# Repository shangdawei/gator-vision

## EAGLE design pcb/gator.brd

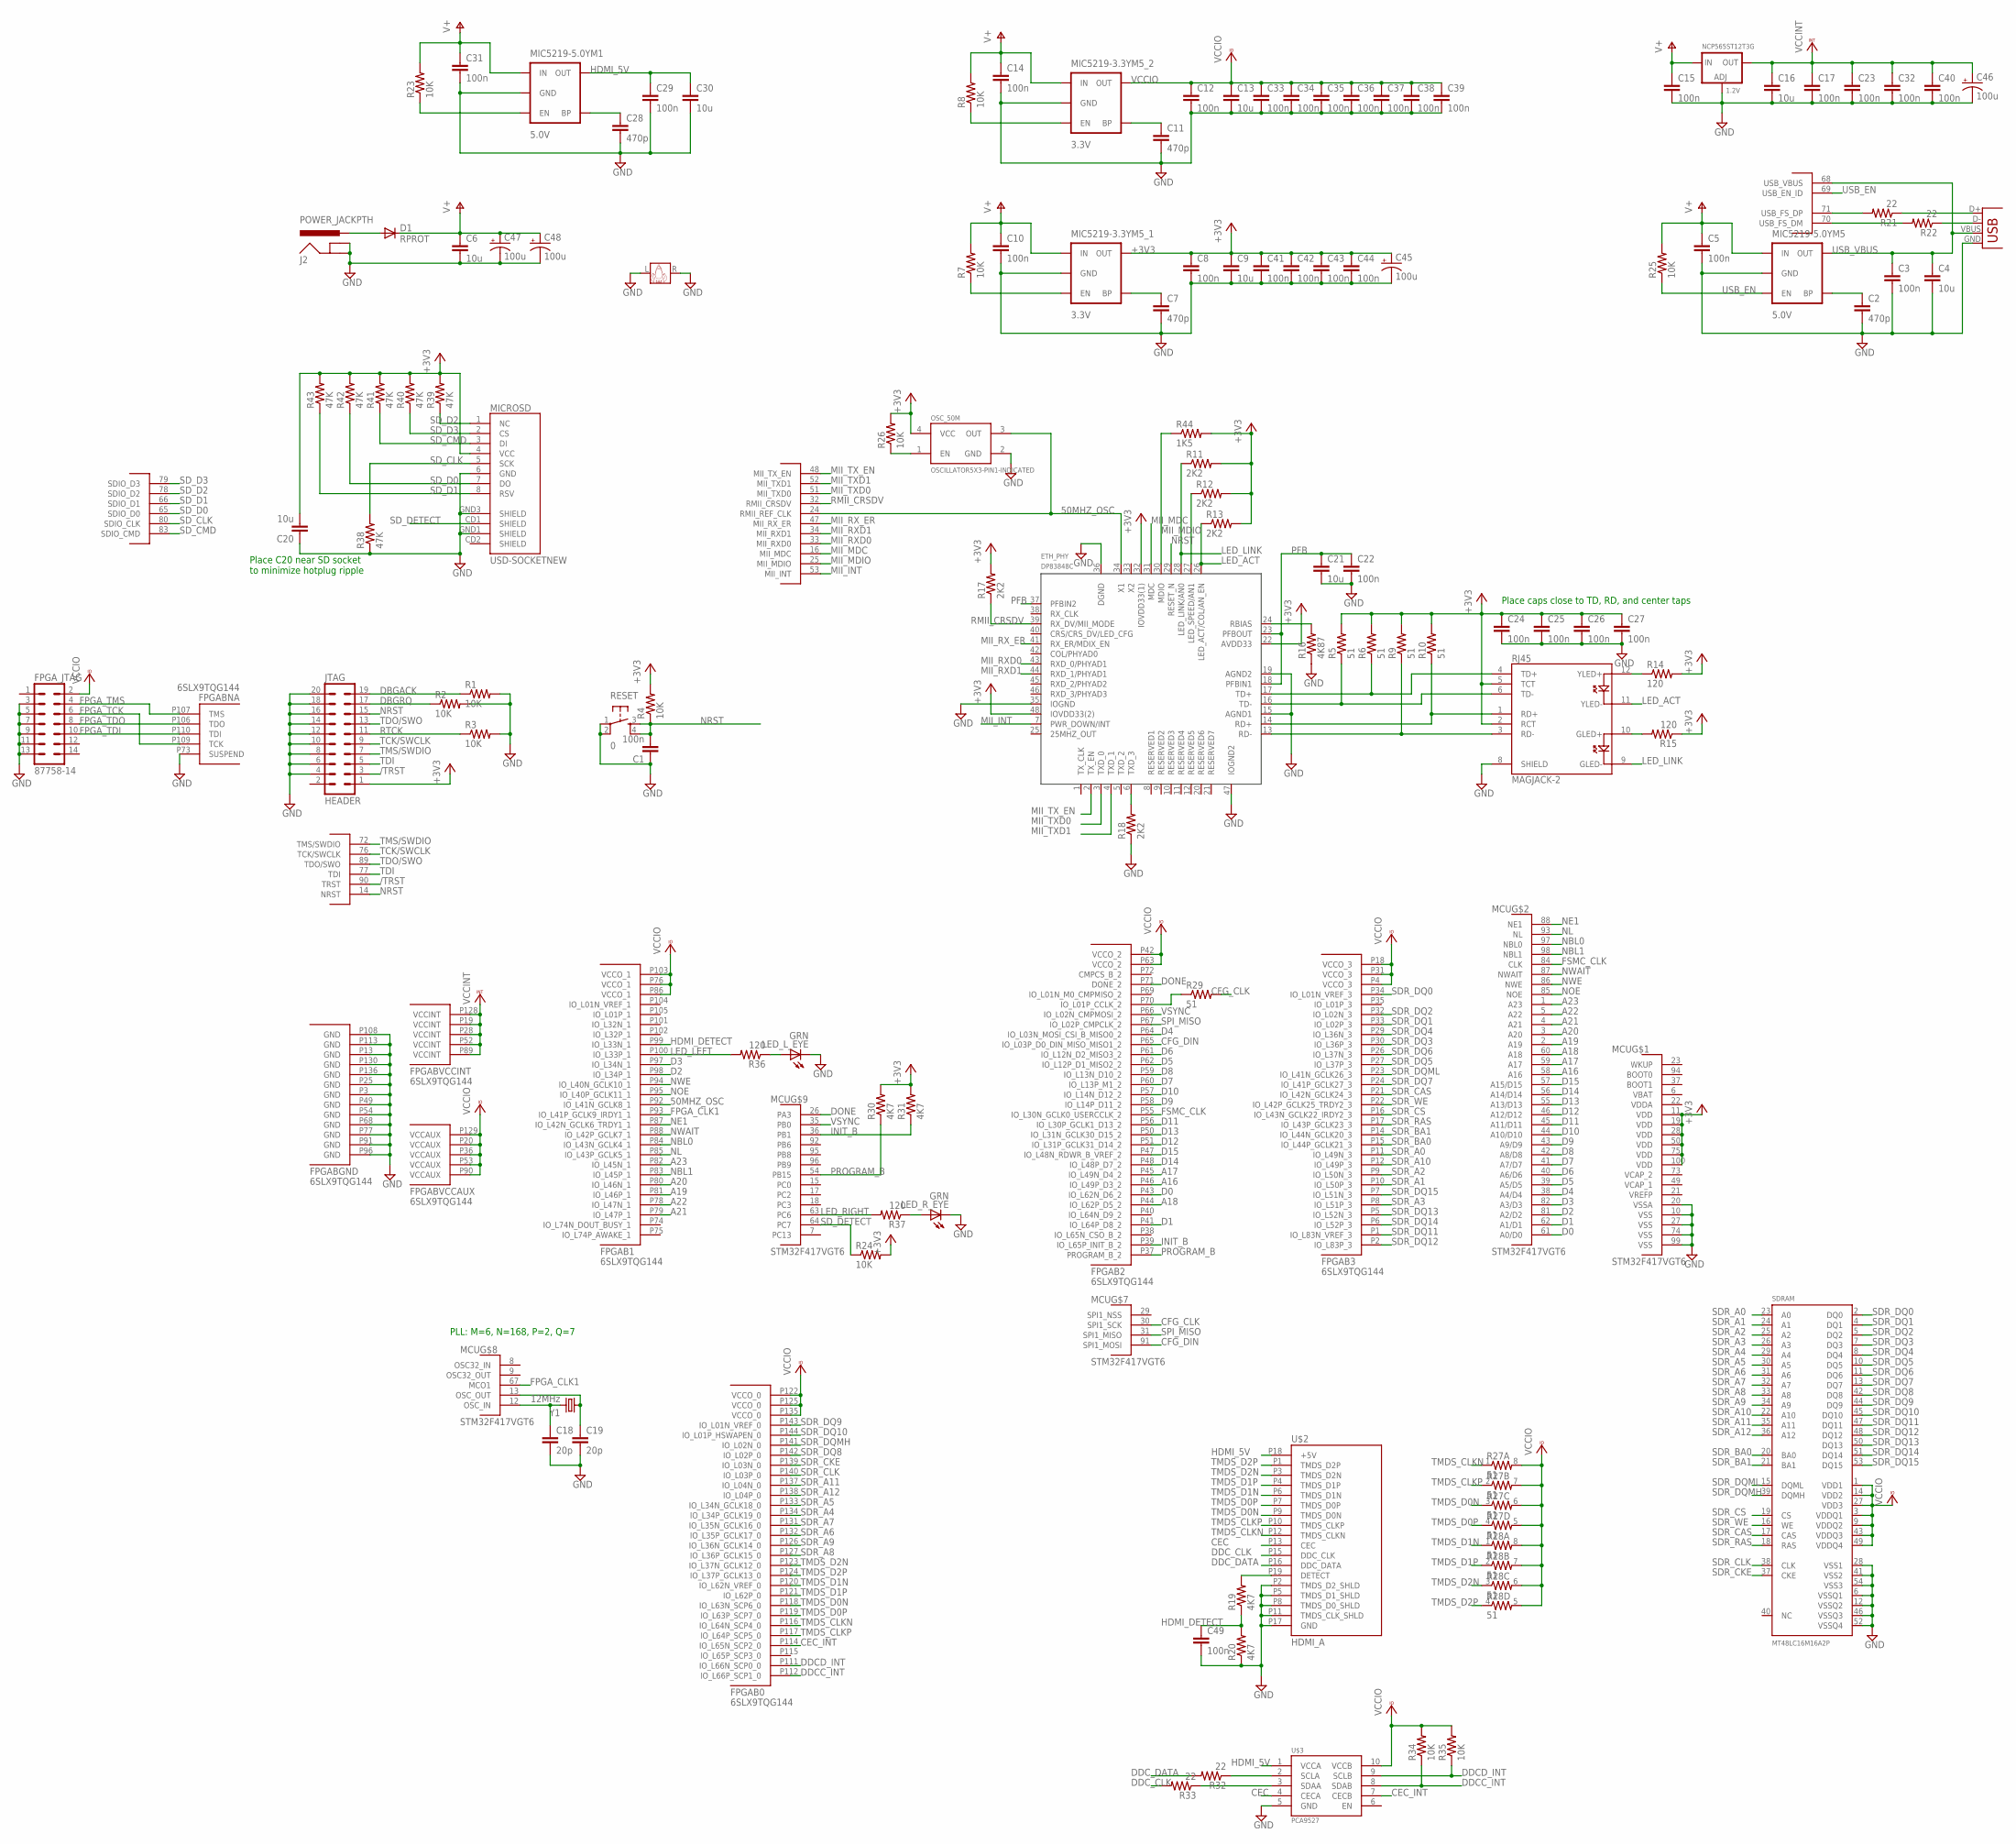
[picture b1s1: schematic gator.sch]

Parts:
C1, C3, C5, C8, C10, C12, C14, C15, C17, C22, C23, C24, C25, C26, C27, C29, C31, C32, C33, C34, C35, C36, C37, C38, C39, C40, C41, C42, C43, C44, C49: 100n; 0603-CAP
C2, C7, C11, C28: 470p; 0603-CAP
C4, C6, C9, C13, C16, C20, C21, C30: 10u; 0603-CAP
C18, C19: 20p; 0603-CAP
C45, C46, C47, C48: 100u; CPOL-RADIAL-100UF-25V
D1: RPROT; DIODE-1N4001; DIGIKEY# 497-6588-1-ND
ETH_PHY: DP83848C; LQFP-48; MOUSER# 926-DP83848CVVX/NOPB; DIGIKEY# DP83848CVVX/NOPBCT-ND
FPGA: 6SLX9TQG144; TQ144; DIGIKEY# 122-1745-ND
FPGA_JTAG: 87758-14; DIGIKEY# AE10561-ND
J2: POWER_JACKPTH; POWER_JACK_PTH; DIGIKEY# CP-002A-ND
JTAG: HEADER; ML20; DIGIKEY# S9172-ND
LED_L_EYE: GRN; LED3MM; DIGIKEY# 160-1659-ND
LED_R_EYE: GRN; LED3MM; DIGIKEY# 160-1659-ND
MCU: STM32F417VGT6; LQFP-100; DIGIKEY# 497-11900-ND
MIC5219-3.3YM5_1, MIC5219-3.3YM5_2: 3.3V; SOT23-5; DIGIKEY# 576-1281-1-ND
MIC5219-5.0YM1, MIC5219-5.0YM5: 5.0V; SOT23-5; DIGIKEY# 576-2770-1-ND
MICROSD: USD-SOCKETNEW; MICRO-SD-SOCKET-PP; DIGIKEY# 101-00660-68-6-1-ND
NCP565ST12T3G: 1.2V; SOT223-R; DIGIKEY# NCP565ST12T3GOSCT-ND
OSC_50M: OSCILLATOR5X3-PIN1-INDICATED; CRYSTAL-OSC-SMD-5X3; DIGIKEY# CTX1011CT-ND
R1, R2, R3, R4, R7, R8, R23, R24, R25, R26, R34, R35: 10K; 0603-RES
R5, R6, R9, R10, R29: 51; 0603-RES
R11, R12, R13, R17, R18: 2K2; 0603-RES
R14, R15, R36, R37: 120; 0603-RES
R16: 4K87; 0603-RES
R19, R20, R30, R31: 4K7; 0603-RES
R21, R22, R32, R33: 22; 0603-RES
R27, R28: 51; 0603-ARV; DIGIKEY# YC164J-51CT-ND
R38, R39, R40, R41, R42, R43: 47K; 0603-RES
R44: 1K5; 0603-RES
RESET: 0; TACTILE-PTH
RJ45: MAGJACK-2; MAGJACK-19938; DIGIKEY# 380-1103-ND
SDRAM: MT48LC16M16A2P; TSOP54-400; MOUSER# 913-AS4C16M16S-6TAN; DIGIKEY# 557-1223-1-ND
U$2: HDMI_A; HDMI_A_SMT; DIGIKEY# WM19084CT-ND
U$3: PCA9527; TSSOP10; DIGIKEY# 568-4770-1-ND
U$4: GATOR_HEAD; DIGIKEY# T1065-P5P-ND
X1: USB-A-S; DIGIKEY# 1175-1016-ND
Y1: 12MHz; HC49US; DIGIKEY# CTX904-ND

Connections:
50MHZ_OSC: ETH_PHY.34 (X1), FPGA.P92 (IO_L41N_GCLK8_1), MCU.24 (RMII_REF_CLK), OSC_50M.3 (OUT)
+3V3: C8.1, C9.1, C20.2, C24.1, C25.1, C26.1, C27.1, C41.1, C42.1, C43.1, C44.1, C45.1 (+), ETH_PHY.22 (AVDD33), ETH_PHY.32 (IOVDD33(1)), ETH_PHY.48 (IOVDD33(2)), JTAG.1, MCU.11 (VDD), MCU.19 (VDD), MCU.28 (VDD), MCU.50 (VDD), MCU.75 (VDD), MCU.100 (VDD), MIC5219-3.3YM5_1.5 (OUT), MICROSD.4 (VCC), OSC_50M.4 (VCC), R4.2, R5.2, R6.2, R9.2, R10.2, R11.2, R12.2, R13.2, R14.2, R15.1, R17.2, R24.2, R26.2, R30.2, R31.2, R39.2, R40.2, R41.2, R42.2, R43.2, R44.2, RJ45.2 (RCT), RJ45.5 (TCT)
/TRST: JTAG.3, MCU.90 (TRST)
A16: FPGA.P46 (IO_L49P_D3_2), MCU.58 (A16)
A17: FPGA.P45 (IO_L49N_D4_2), MCU.59 (A17)
A18: FPGA.P44 (IO_L62P_D5_2), MCU.60 (A18)
A19: FPGA.P81 (IO_L46P_1), MCU.2 (A19)
A20: FPGA.P80 (IO_L46N_1), MCU.3 (A20)
A21: FPGA.P79 (IO_L47P_1), MCU.4 (A21)
A22: FPGA.P78 (IO_L47N_1), MCU.5 (A22)
A23: FPGA.P82 (IO_L45N_1), MCU.1 (A23)
CEC: U$2.P13 (CEC), U$3.4 (CECA)
CEC_INT: FPGA.P114 (IO_L65N_SCP2_0), U$3.7 (CECB)
CFG_CLK: MCU.30 (SPI1_SCK), R29.2
CFG_DIN: FPGA.P65 (IO_L03P_D0_DIN_MISO_MISO1_2), MCU.91 (SPI1_MOSI)
D0: FPGA.P43 (IO_L62N_D6_2), MCU.61 (A0/D0)
D1: FPGA.P41 (IO_L64P_D8_2), MCU.62 (A1/D1)
D2: FPGA.P98 (IO_L34P_1), MCU.81 (A2/D2)
D3: FPGA.P97 (IO_L34N_1), MCU.82 (A3/D3)
D4: FPGA.P64 (IO_L03N_MOSI_CSI_B_MISO0_2), MCU.38 (A4/D4)
D5: FPGA.P62 (IO_L12P_D1_MISO2_2), MCU.39 (A5/D5)
D6: FPGA.P61 (IO_L12N_D2_MISO3_2), MCU.40 (A6/D6)
D7: FPGA.P60 (IO_L13P_M1_2), MCU.41 (A7/D7)
D8: FPGA.P59 (IO_L13N_D10_2), MCU.42 (A8/D8)
D9: FPGA.P58 (IO_L14P_D11_2), MCU.43 (A9/D9)
D10: FPGA.P57 (IO_L14N_D12_2), MCU.44 (A10/D10)
D11: FPGA.P56 (IO_L30P_GCLK1_D13_2), MCU.45 (A11/D11)
D12: FPGA.P51 (IO_L31P_GCLK31_D14_2), MCU.46 (A12/D12)
D13: FPGA.P50 (IO_L31N_GCLK30_D15_2), MCU.55 (A13/D13)
D14: FPGA.P48 (IO_L48P_D7_2), MCU.56 (A14/D14)
D15: FPGA.P47 (IO_L48N_RDWR_B_VREF_2), MCU.57 (A15/D15)
DBGACK: JTAG.19, R1.1
DBGRQ: JTAG.17, R2.1
DDCC_INT: FPGA.P112 (IO_L66P_SCP1_0), R34.1, U$3.8 (SDAB)
DDCD_INT: FPGA.P111 (IO_L66N_SCP0_0), R35.1, U$3.9 (SCLB)
DDC_CLK: R33.2, U$2.P15 (DDC_CLK)
DDC_DATA: R32.2, U$2.P16 (DDC_DATA)
DONE: FPGA.P71 (DONE_2), MCU.26 (PA3)
FPGA_CLK1: FPGA.P93 (IO_L41P_GCLK9_IRDY1_1), MCU.67 (MCO1)
FPGA_TCK: FPGA.P109 (TCK), FPGA_JTAG.6
FPGA_TDI: FPGA.P110 (TDI), FPGA_JTAG.10
FPGA_TDO: FPGA.P106 (TDO), FPGA_JTAG.8
FPGA_TMS: FPGA.P107 (TMS), FPGA_JTAG.4
FSMC_CLK: FPGA.P55 (IO_L30N_GCLK0_USERCCLK_2), MCU.84 (CLK)
GND: C1.1, C2.2, C3.2, C4.2, C5.2, C6.2, C7.2, C8.2, C9.2, C10.2, C11.2, C12.2, C13.2, C14.2, C15.2, C16.2, C17.2, C18.2, C19.2, C20.1, C21.2, C22.2, C23.2, C24.2, C25.2, C26.2, C27.2, C28.2, C29.2, C30.2, C31.2, C32.2, C33.2, C34.2, C35.2, C36.2, C37.2, C38.2, C39.2, C40.2, C41.2, C42.2, C43.2, C44.2, C45.2 (-), C46.2 (-), C47.2 (-), C48.2 (-), C49.2, ETH_PHY.15 (AGND1), ETH_PHY.19 (AGND2), ETH_PHY.35 (IOGND), ETH_PHY.36 (DGND), ETH_PHY.47 (IOGND2), FPGA.P3 (GND), FPGA.P13 (GND), FPGA.P25 (GND), FPGA.P49 (GND), FPGA.P54 (GND), FPGA.P68 (GND), FPGA.P73 (SUSPEND), FPGA.P77 (GND), FPGA.P91 (GND), FPGA.P96 (GND), FPGA.P108 (GND), FPGA.P113 (GND), FPGA.P130 (GND), FPGA.P136 (GND), FPGA_JTAG.3, FPGA_JTAG.5, FPGA_JTAG.7, FPGA_JTAG.9, FPGA_JTAG.11, FPGA_JTAG.13, J2.GND, J2.GNDBREAK, JTAG.4, JTAG.6, JTAG.8, JTAG.10, JTAG.12, JTAG.14, JTAG.16, JTAG.18, JTAG.20, LED_L_EYE.K (C), LED_R_EYE.K (C), MCU.10 (VSS), MCU.20 (VSSA), MCU.27 (VSS), MCU.74 (VSS), MCU.99 (VSS), MIC5219-3.3YM5_1.2 (GND), MIC5219-3.3YM5_2.2 (GND), MIC5219-5.0YM1.2 (GND), MIC5219-5.0YM5.2 (GND), MICROSD.6 (GND), MICROSD.GND1 (SHIELD), MICROSD.GND3 (SHIELD), NCP565ST12T3G.1 (ADJ), OSC_50M.2 (GND), R1.2, R2.2, R3.2, R16.1, R18.1, R20.1, R38.1, RESET.1, RESET.2, RJ45.8 (SHIELD), SDRAM.6 (VSSQ1), SDRAM.12 (VSSQ2), SDRAM.28 (VSS1), SDRAM.41 (VSS2), SDRAM.46 (VSSQ3), SDRAM.52 (VSSQ4), SDRAM.54 (VSS3), U$2.P2 (TMDS_D2_SHLD), U$2.P5 (TMDS_D1_SHLD), U$2.P8 (TMDS_D0_SHLD), U$2.P11 (TMDS_CLK_SHLD), U$2.P17 (GND), U$3.5 (GND), U$4.L, U$4.R, X1.GND
HDMI_5V: C29.1, C30.1, MIC5219-5.0YM1.5 (OUT), U$2.P18 (+5V), U$3.1 (VCCA)
HDMI_DETECT: C49.1, FPGA.P99 (IO_L33N_1), R19.1, R20.2
INIT_B: FPGA.P39 (IO_L65P_INIT_B_2), MCU.36 (PB1), R31.1
LED_ACT: ETH_PHY.26 (LED_ACT/COL/AN_EN), R13.1, RJ45.11 (YLED-)
LED_LEFT: FPGA.P100 (IO_L33P_1), R36.2
LED_LINK: ETH_PHY.28 (LED_LINK/AN0), R11.1, RJ45.9 (GLED-)
LED_RIGHT: MCU.63 (PC6), R37.2
MII_INT: ETH_PHY.7 (PWR_DOWN/INT), MCU.53 (MII_INT)
MII_MDC: ETH_PHY.31 (MDC), MCU.16 (MII_MDC)
MII_MDIO: ETH_PHY.30 (MDIO), MCU.25 (MII_MDIO), R44.1
MII_RXD0: ETH_PHY.43 (RXD_0/PHYAD1), MCU.33 (MII_RXD0)
MII_RXD1: ETH_PHY.44 (RXD_1/PHYAD1), MCU.34 (MII_RXD1)
MII_RX_ER: ETH_PHY.41 (RX_ER/MDIX_EN), MCU.47 (MII_RX_ER)
MII_TXD0: ETH_PHY.3 (TXD_0), MCU.51 (MII_TXD0)
MII_TXD1: ETH_PHY.4 (TXD_1), MCU.52 (MII_TXD1)
MII_TX_EN: ETH_PHY.2 (TX_EN), MCU.48 (MII_TX_EN)
unnamed: MCU.71 (USB_FS_DP), R21.2
unnamed: MCU.70 (USB_FS_DM), R22.2
unnamed: D1.A, J2.PWR
unnamed: C2.1, MIC5219-5.0YM5.4 (BP)
unnamed: MIC5219-3.3YM5_1.3 (EN), R7.1
unnamed: C7.1, MIC5219-3.3YM5_1.4 (BP)
unnamed: MIC5219-3.3YM5_2.3 (EN), R8.1
unnamed: R32.1, U$3.2 (SCLA)
unnamed: R33.1, U$3.3 (SDAA)
unnamed: LED_L_EYE.A, R36.1
unnamed: LED_R_EYE.A, R37.1
unnamed: R14.1, RJ45.12 (YLED+)
unnamed: R15.2, RJ45.10 (GLED+)
unnamed: C28.1, MIC5219-5.0YM1.4 (BP)
unnamed: ETH_PHY.24 (RBIAS), R16.2
unnamed: ETH_PHY.27 (LED_SPEED/AN1), R12.1
unnamed: ETH_PHY.6 (TXD_3), R18.2
unnamed: R21.1, X1.D+
unnamed: R22.1, X1.D-
unnamed: MIC5219-5.0YM1.3 (EN), R23.1
unnamed: R19.2, U$2.P19 (DETECT)
unnamed: C18.1, MCU.12 (OSC_IN), Y1.2
unnamed: C19.1, MCU.13 (OSC_OUT), Y1.1
unnamed: OSC_50M.1 (EN), R26.1
unnamed: FPGA.P70 (IO_L01P_CCLK_2), R29.1
unnamed: C11.1, MIC5219-3.3YM5_2.4 (BP)
NBL0: FPGA.P84 (IO_L43N_GCLK4_1), MCU.97 (NBL0)
NBL1: FPGA.P83 (IO_L45P_1), MCU.98 (NBL1)
NE1: FPGA.P87 (IO_L42N_GCLK6_TRDY1_1), MCU.88 (NE1)
NL: FPGA.P85 (IO_L43P_GCLK5_1), MCU.93 (NL)
NOE: FPGA.P95 (IO_L40P_GCLK11_1), MCU.85 (NOE)
NRST: C1.2, ETH_PHY.29 (RESET_N), JTAG.15, MCU.14 (NRST), R4.1, RESET.3, RESET.4
NWAIT: FPGA.P88 (IO_L42P_GCLK7_1), MCU.87 (NWAIT)
NWE: FPGA.P94 (IO_L40N_GCLK10_1), MCU.86 (NWE)
PFB: C21.1, C22.1, ETH_PHY.18 (PFBIN1), ETH_PHY.23 (PFBOUT), ETH_PHY.37 (PFBIN2)
PROGRAM_B: FPGA.P37 (PROGRAM_B_2), MCU.54 (PB15), R30.1
RD+: ETH_PHY.14 (RD+), R10.1, RJ45.1 (RD+)
RD-: ETH_PHY.13 (RD-), R9.1, RJ45.3 (RD-)
RMII_CRSDV: ETH_PHY.39 (RX_DV/MII_MODE), MCU.32 (RMII_CRSDV), R17.1
RTCK: JTAG.11, R3.1
SDR_A0: FPGA.P11 (IO_L49N_3), SDRAM.23 (A0)
SDR_A1: FPGA.P10 (IO_L50P_3), SDRAM.24 (A1)
SDR_A2: FPGA.P9 (IO_L50N_3), SDRAM.25 (A2)
SDR_A3: FPGA.P8 (IO_L51P_3), SDRAM.26 (A3)
SDR_A4: FPGA.P134 (IO_L34P_GCLK19_0), SDRAM.29 (A4)
SDR_A5: FPGA.P133 (IO_L34N_GCLK18_0), SDRAM.30 (A5)
SDR_A6: FPGA.P132 (IO_L35P_GCLK17_0), SDRAM.31 (A6)
SDR_A7: FPGA.P131 (IO_L35N_GCLK16_0), SDRAM.32 (A7)
SDR_A8: FPGA.P127 (IO_L36P_GCLK15_0), SDRAM.33 (A8)
SDR_A9: FPGA.P126 (IO_L36N_GCLK14_0), SDRAM.34 (A9)
SDR_A10: FPGA.P12 (IO_L49P_3), SDRAM.22 (A10)
SDR_A11: FPGA.P137 (IO_L04N_0), SDRAM.35 (A11)
SDR_A12: FPGA.P138 (IO_L04P_0), SDRAM.36 (A12)
SDR_BA0: FPGA.P15 (IO_L44P_GCLK21_3), SDRAM.20 (BA0)
SDR_BA1: FPGA.P14 (IO_L44N_GCLK20_3), SDRAM.21 (BA1)
SDR_CAS: FPGA.P21 (IO_L42N_GCLK24_3), SDRAM.17 (CAS)
SDR_CKE: FPGA.P139 (IO_L03N_0), SDRAM.37 (CKE)
SDR_CLK: FPGA.P140 (IO_L03P_0), SDRAM.38 (CLK)
SDR_CS: FPGA.P16 (IO_L43N_GCLK22_IRDY2_3), SDRAM.19 (CS)
SDR_DQ0: FPGA.P34 (IO_L01N_VREF_3), SDRAM.2 (DQ0)
SDR_DQ1: FPGA.P33 (IO_L02P_3), SDRAM.4 (DQ1)
SDR_DQ2: FPGA.P32 (IO_L02N_3), SDRAM.5 (DQ2)
SDR_DQ3: FPGA.P30 (IO_L36P_3), SDRAM.7 (DQ3)
SDR_DQ4: FPGA.P29 (IO_L36N_3), SDRAM.8 (DQ4)
SDR_DQ5: FPGA.P27 (IO_L37P_3), SDRAM.10 (DQ5)
SDR_DQ6: FPGA.P26 (IO_L37N_3), SDRAM.11 (DQ6)
SDR_DQ7: FPGA.P24 (IO_L41P_GCLK27_3), SDRAM.13 (DQ7)
SDR_DQ8: FPGA.P142 (IO_L02P_0), SDRAM.42 (DQ8)
SDR_DQ9: FPGA.P143 (IO_L01N_VREF_0), SDRAM.44 (DQ9)
SDR_DQ10: FPGA.P144 (IO_L01P_HSWAPEN_0), SDRAM.45 (DQ10)
SDR_DQ11: FPGA.P1 (IO_L83N_VREF_3), SDRAM.47 (DQ11)
SDR_DQ12: FPGA.P2 (IO_L83P_3), SDRAM.48 (DQ12)
SDR_DQ13: FPGA.P5 (IO_L52N_3), SDRAM.50 (DQ13)
SDR_DQ14: FPGA.P6 (IO_L52P_3), SDRAM.51 (DQ14)
SDR_DQ15: FPGA.P7 (IO_L51N_3), SDRAM.53 (DQ15)
SDR_DQMH: FPGA.P141 (IO_L02N_0), SDRAM.39 (DQMH)
SDR_DQML: FPGA.P23 (IO_L41N_GCLK26_3), SDRAM.15 (DQML)
SDR_RAS: FPGA.P17 (IO_L43P_GCLK23_3), SDRAM.18 (RAS)
SDR_WE: FPGA.P22 (IO_L42P_GCLK25_TRDY2_3), SDRAM.16 (WE)
SD_CLK: MCU.80 (SDIO_CLK), MICROSD.5 (SCK), R38.2
SD_CMD: MCU.83 (SDIO_CMD), MICROSD.3 (DI), R41.1
SD_D0: MCU.65 (SDIO_D0), MICROSD.7 (DO), R42.1
SD_D1: MCU.66 (SDIO_D1), MICROSD.8 (RSV), R43.1
SD_D2: MCU.78 (SDIO_D2), MICROSD.1 (NC), R39.1
SD_D3: MCU.79 (SDIO_D3), MICROSD.2 (CS), R40.1
SD_DETECT: MCU.64 (PC7), MICROSD.CD1 (SHIELD), R24.1
SPI_MISO: FPGA.P67 (IO_L02P_CMPCLK_2), MCU.31 (SPI1_MISO)
TCK/SWCLK: JTAG.9, MCU.76 (TCK/SWCLK)
TD+: ETH_PHY.17 (TD+), R6.1, RJ45.4 (TD+)
TD-: ETH_PHY.16 (TD-), R5.1, RJ45.6 (TD-)
TDI: JTAG.5, MCU.77 (TDI)
TDO/SWO: JTAG.13, MCU.89 (TDO/SWO)
TMDS_CLKN: FPGA.P116 (IO_L64N_SCP4_0), R27.1, U$2.P12 (TMDS_CLKN)
TMDS_CLKP: FPGA.P117 (IO_L64P_SCP5_0), R27.2 (1), U$2.P10 (TMDS_CLKP)
TMDS_D0N: FPGA.P118 (IO_L63N_SCP6_0), R27.3 (1), U$2.P9 (TMDS_D0N)
TMDS_D0P: FPGA.P119 (IO_L63P_SCP7_0), R27.4 (1), U$2.P7 (TMDS_D0P)
TMDS_D1N: FPGA.P120 (IO_L62N_VREF_0), R28.1, U$2.P6 (TMDS_D1N)
TMDS_D1P: FPGA.P121 (IO_L62P_0), R28.2 (1), U$2.P4 (TMDS_D1P)
TMDS_D2N: FPGA.P123 (IO_L37N_GCLK12_0), R28.3 (1), U$2.P3 (TMDS_D2N)
TMDS_D2P: FPGA.P124 (IO_L37P_GCLK13_0), R28.4 (1), U$2.P1 (TMDS_D2P)
TMS/SWDIO: JTAG.7, MCU.72 (TMS/SWDIO)
USB_EN: MCU.69 (USB_EN_ID), MIC5219-5.0YM5.3 (EN), R25.1
USB_VBUS: C3.1, C4.1, MCU.68 (USB_VBUS), MIC5219-5.0YM5.5 (OUT), X1.VBUS
V+: C5.1, C6.1, C10.1, C14.1, C15.1, C31.1, C47.1 (+), C48.1 (+), D1.C, MIC5219-3.3YM5_1.1 (IN), MIC5219-3.3YM5_2.1 (IN), MIC5219-5.0YM1.1 (IN), MIC5219-5.0YM5.1 (IN), NCP565ST12T3G.3 (IN), R7.2, R8.2, R23.2, R25.2
VCCINT: C16.1, C17.1, C23.1, C32.1, C40.1, C46.1 (+), FPGA.P19 (VCCINT), FPGA.P28 (VCCINT), FPGA.P52 (VCCINT), FPGA.P89 (VCCINT), FPGA.P128 (VCCINT), NCP565ST12T3G.2 (OUT)
VCCIO: C12.1, C13.1, C33.1, C34.1, C35.1, C36.1, C37.1, C38.1, C39.1, FPGA.P4 (VCCO_3), FPGA.P18 (VCCO_3), FPGA.P20 (VCCAUX), FPGA.P31 (VCCO_3), FPGA.P36 (VCCAUX), FPGA.P42 (VCCO_2), FPGA.P53 (VCCAUX), FPGA.P63 (VCCO_2), FPGA.P76 (VCCO_1), FPGA.P86 (VCCO_1), FPGA.P90 (VCCAUX), FPGA.P103 (VCCO_1), FPGA.P122 (VCCO_0), FPGA.P125 (VCCO_0), FPGA.P129 (VCCAUX), FPGA.P135 (VCCO_0), FPGA_JTAG.2, MIC5219-3.3YM5_2.5 (OUT), R27.5 (2), R27.6 (2), R27.7 (2), R27.8 (2), R28.5 (2), R28.6 (2), R28.7 (2), R28.8 (2), R34.2, R35.2, SDRAM.1 (VDD1), SDRAM.3 (VDDQ1), SDRAM.9 (VDDQ2), SDRAM.14 (VDD2), SDRAM.27 (VDD3), SDRAM.43 (VDDQ3), SDRAM.49 (VDDQ4), U$3.10 (VCCB)
VSYNC: FPGA.P66 (IO_L02N_CMPMOSI_2), MCU.35 (PB0)

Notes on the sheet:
PLL: M=6, N=168, P=2, Q=7
Place C20 near SD socket to minimize hotplug ripple
Place caps close to TD, RD, and center taps

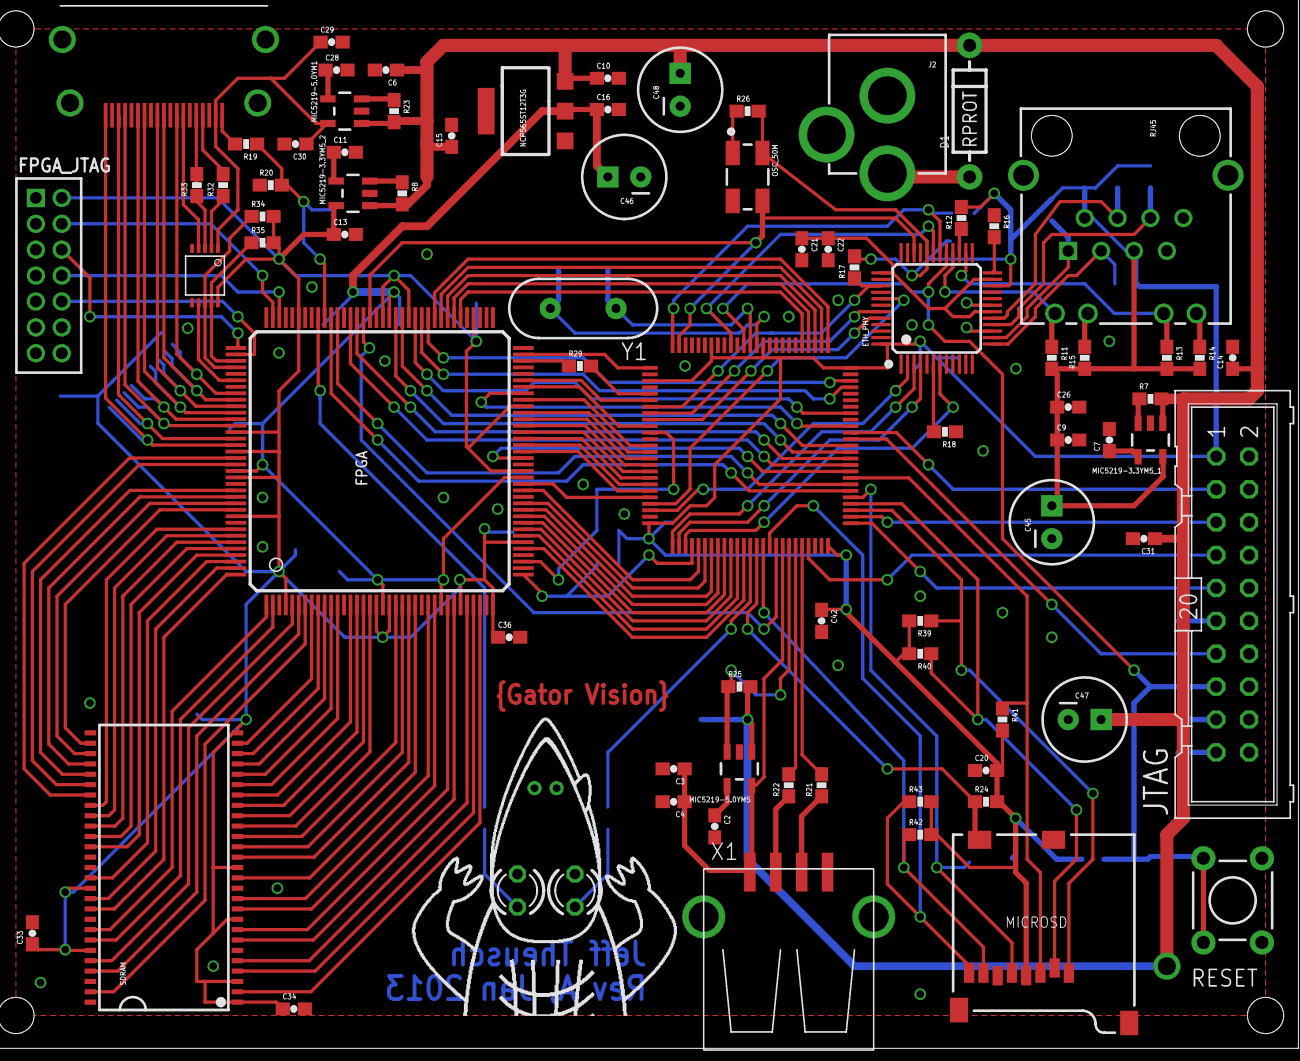
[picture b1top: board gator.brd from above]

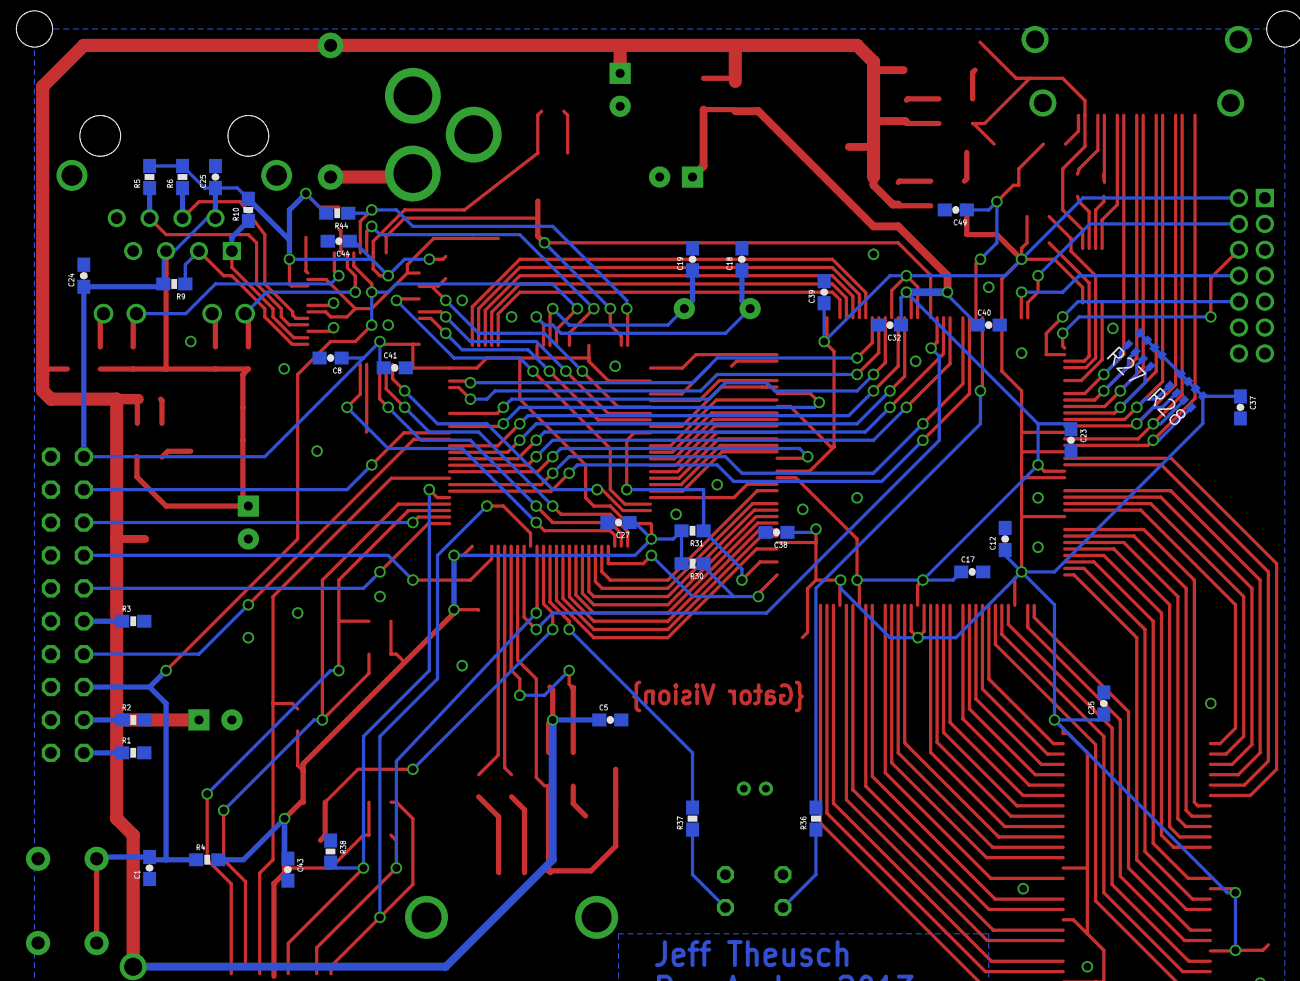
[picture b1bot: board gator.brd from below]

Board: 2 copper layers, 117 parts (37 on the bottom side), 168 nets.

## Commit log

2012-05-27 Initial directory structure.
2012-08-07 Added pcb folder
2012-08-07 Added blank Eagle project for gator pcb
2012-08-07 Added sparkfun libraries
2012-08-10 Added reference projects and initial gator library
2012-08-10 Removed silly backup save files
2012-08-18 added some more libraries, refactored design to eliminate hdmi transmitter
2012-08-18 Added papilio wing templates for expansion headers
2012-08-20 Migrated to Spartan 6 and added more parts
2012-08-21 Added more pin assignments to ATM32F417 part. Still need to assign SPI and stuff like clocks
2012-08-23 Added SPI and clock pins to cortex part
2012-08-25 Finished arm cortex part
2012-08-27 Assigned many of the FPGA pins, cleaned up HDMI connector
2012-09-06 Added SDRAM part and connected it to FPGA
2012-09-18 Connected FSMC; 8-bit Papilio wing
2012-09-24 Wired up some of the ethernet RMII
2012-10-08 Cleaned up power supplies and connected usb and micro sd
2012-10-08 more power supply cleanup
2012-10-08 Added a bunch of autosave files to ignore list
2012-10-30 Added HDMI termination, oscillators, improved routing
2012-11-28 Routed power for SDRAM
2012-11-28 Routed some FPGA power and added back ground plane
2012-11-29 Finished routing power for FPGA and microcontroller
2012-11-29 Added INIT_B and PROGRAM_B signals needed for slave serial configuration
2012-12-14 Routed power to ARM, added VSync signal
2012-12-23 any recent changes before break
2012-12-25 Routed and cleaned up USB power, SD card signals, ethernet phy
2012-12-25 Finished routing ethernet
2012-12-26 Finished routing CEC, DDC, and remaining power; still have to do decoupling caps
2012-12-26 More power supply cleanup; 3 airwires remaining
2012-12-26 Minor cleanup; added signals for eyes; still need decoupling caps
2012-12-27 Added gator and his eyeballs
2012-12-27 Added original gator art to repo for safekeeping
2012-12-28 Added source trees for FatFS, FreeRTOS, and lwIP
2012-12-28 Solved all ERC warnings and connected all airwires
2012-12-28 Added initial CAM job and gerbers
2012-12-28 Solved all DRC assuming 6mil min spacing
2012-12-28 Made DRC pass with 10mil min trace width
2012-12-28 saving board till I hear back from batchpcb
2012-12-30 Latest CAM and DRC settings
2012-12-31 Added tons of decoupling capacitors
2013-01-03 Added Fusion DRC and CAM settings; added SD SCLK pulldown; added large power supply caps
2013-01-03 Renamed some parts for clarity
2013-01-03 Moved FSMC_CLK to a clock input on the FPGA
2013-01-08 Added pull-ups for sd card and ethernet
2013-01-22 Generated Rev A gerbers
2013-01-22 Tagged PCB_RevA
2013-01-31 Added licenses and initial design doc
2013-02-02 Added STM32 libraries from eval board source code - CMSIS, USB Host, USB OTG, StdPeriph
2013-02-02 Added STM32 ethernet driver and ST license agreement
2013-02-03 Added initial, successfully building ARM Eclipse project
2013-02-03 Updated CMSIS and standard peripherals library
2013-02-03 Updated include path after updating standard peripherals library
2013-02-03 Working blinky lights, no FreeRTOS yet
2013-02-06 Added local compiled copy of OpenOCD
2013-02-09 Known working launch settings for debug and OpenOCD; Changed LED blinks to prove updates
2013-02-09 Added "boot" dir for FatFs boot loader project
2013-02-09 Added externals to borrow FatFs and STM32Libraries from system to boot
2013-02-09 Fixed weird eclipse gcc options issue; changed to blink one LED in the main loop; not building completely yet
2013-02-09 started freertos task scheduler
2013-02-11 Added some project organization with config and tasks dirs
2013-02-11 Added port configuration definitions and code
2013-02-24 Added errata document
2013-02-24 Made 1 Hz flasher run under a FreeRTOS timer and task
2013-02-25 Included lwip in system code project
2013-02-25 Fixed a couple compiler warnings due to an unused local
2013-03-04 Added errata comment to use cheaper HDMI connector
2013-03-04 Added errata note to add bypass cap to oscillator
2013-03-04 Added errata note to add silkscreen stuff
2013-03-04 Added Digikey parts for everything except resistors and capacitors
2013-03-06 Finished adding DigiKey part numbers to schematic
2013-06-15 Cleaned up directory organization, and suppressed remaining compiler warnings
2013-06-15 Updated include paths
2013-06-15 Corrected svn:externals property for boot loader project
2013-06-24 Enabled LWIP_SOCKET and SYS_LIGHTWEIGHT_PROT
2013-06-24 Converted gator-vision-system to a C++ project
2013-06-24 Added FreeRTOS_EC - some pre-made wrapper classes for FreeRTOS/C++
2013-06-24 Re-factored project to use C++ and the FreeRTOS Extension Classes
2013-06-25 Turned on compiler optimization and fixed potential bad array index in dhcp.c
2013-07-05 Added most of the ethernet modules
2013-07-05 Added call to init ports; link and activity lights are blinking
2013-07-06 Turned off AutoIP for now in favor of using a fixed IP, just to get transmit working
2013-07-09 Added zlib so we can use cramfs later
2013-07-10 Added cramfs tools and filesystem root
2013-07-13 Turning off optimization lets ARP resolve addressing correctly
2013-07-13 Using an older version of the eth driver because otherwise a busy wait fails to init the ethernet driver correctly
2013-07-13 Verified that ping kindof works after turning on first level of optimization. Still have to fix ping checksum.
2013-07-13 Confirmed that Optimize Most works just as well; going back to Optimize None for ease of debugging
2013-07-15 Fixed ICMP checksum (using hardware checksum), enabled DHCP/AutoIP
2013-07-16 Added class stubs so it will be easier to fill in the application later
2013-07-16 changed "Copyright" to "Copyleft"
2013-07-17 Refactored class stubs a little after making TCPServer a templated class
2013-07-27 Fixed template syntax in TCPServer class
2013-07-30 Started to elaborate TCPServer and TCPSession
2013-07-30 Elaborated TCPServer a bit more
2013-08-02 Tweaked TCPSession a bit to match what I think to be common use cases
2013-08-25 Archiving initial progress on NetServiceManager, TCPServer, TCPSession, FTPSession - will not build for a while until I get a complete draft for debugging
2013-09-02 Wrote some of AcceptClient
2013-09-04 Finished the basics of TCPServer; code project builds
2013-09-04 More robust handling of link/dhcp up and down
2013-10-12 Modified DHCP behavior to reboot when link status changes
2013-10-12 Added FTPServer task, fixed byte order of bind address, fixed session close behavior
2013-10-12 Added notes to split out the CAN pins for future use, and to power with microusb cell charger
2013-10-13 Starting basic FTP command set; login works
2013-10-13 Added XCUP, XCWD, XMKD, XPWD, XRMD as a reminder to alias these to the standard commands later
2013-10-14 Added link to https://docs.google.com/open?id=0B7OY5pub_GfIa2k2MmFzelZFR1U as a reference example for STM32 SDIO
2013-10-14 Added baseline port for FatFS from the STM32F4 demo builder package
2013-10-14 Added SDIO example code including SD_ReadMultiBlocksFIXED and SD_WriteMultiBlocksFIXED which are supposed to support cards >4GB
2013-12-24 Updated project file with additional settings... not sure if they're actually needed
2013-12-27 Excluding example fatfs port so the project builds
2013-12-28 Made separate OpenOCD launchers for 32-bit and 64-bit
2013-12-28 Updated to FatFS R0.10
2013-12-28 Specified a set of virtual functions for FileSystem class
2013-12-29 Finished stubs for FATFileSystem
2013-12-29 Added some support types for queueing filesystem commands
2014-01-03 Refactored filesystem function definitions to use char arrays instead of stl strings, to reduce heap usage
2014-01-03 Changed FreeRTOS to use heap_1.c which cannot free and uses a dedicated statically allocated memory region
2014-08-19 Made tiny change to test commit access
2015-03-02 Removed documentation for DSP lib
2015-10-25 Migrating wiki contents from Google Code

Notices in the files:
parts and their libraries:
SparkFun-Connectors: Licensing: CC v3.0 Share-Alike You are welcome to use this library for commercial purposes.
con-molex-milli-grid: Copyright (C) 2010, Bob Starr
